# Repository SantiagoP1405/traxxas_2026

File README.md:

# traxxas_2026
Description will be added later.

Clone repository
```
cd
mkdir Workspaces/
cd Workspaces
mkdir traxxas_ws
cd traxxas_ws
git clone https://github.com/SantiagoP1405/traxxas_2026.git
mv traxxas_2026/ src/
colcon build
source install/setup.bash
```

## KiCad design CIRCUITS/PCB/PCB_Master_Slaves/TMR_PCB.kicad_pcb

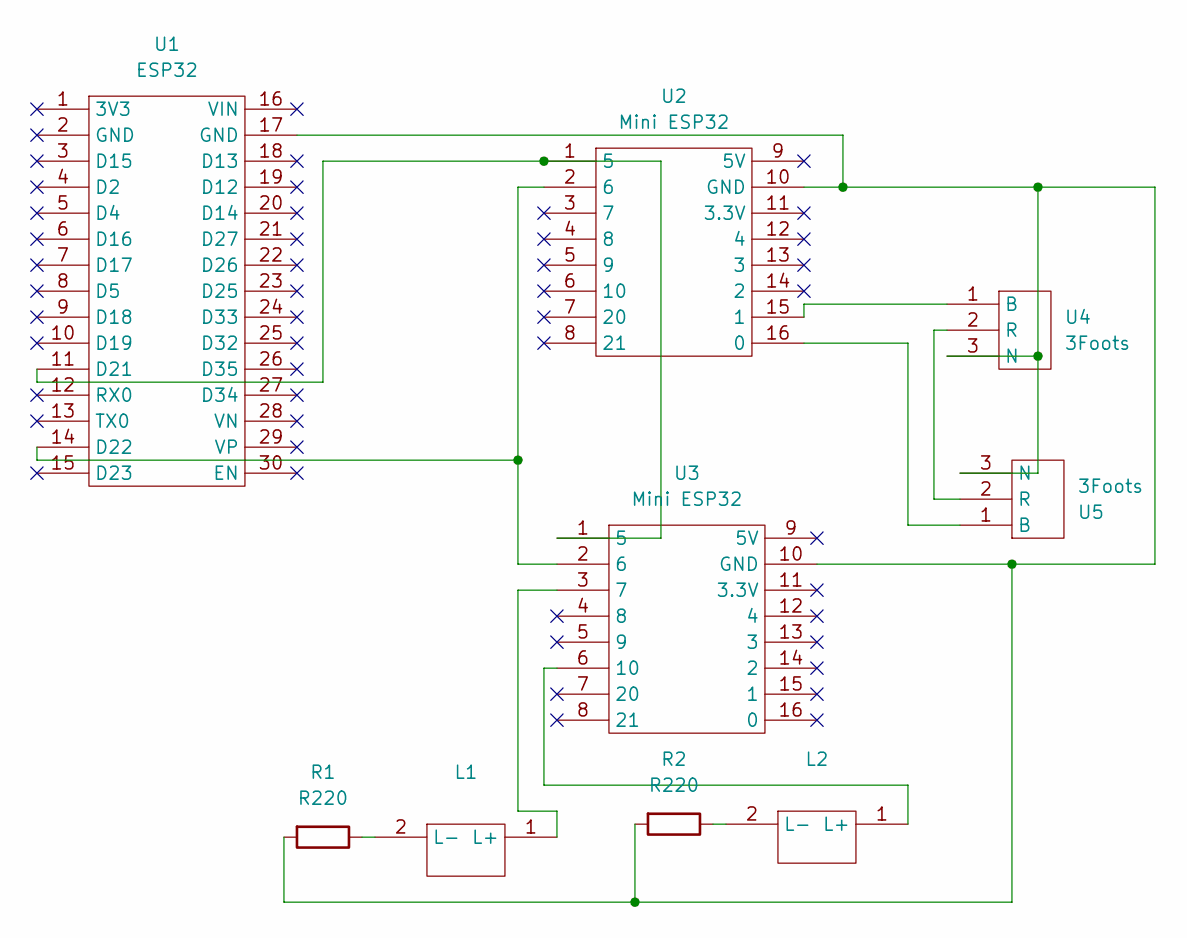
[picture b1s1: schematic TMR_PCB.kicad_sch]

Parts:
L1, L2: Leds
R1, R2: R220; R_Axial_DIN0207_L6.3mm_D2.5mm_P7.62mm_Horizontal
U1: ESP32
U2, U3: Mini ESP32
U4, U5: 3Foots

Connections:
unnamed: L1.1 (L+), U3.3 (7)
unnamed: L1.2 (L-), R1.1
unnamed: L2.1 (L+), U3.6 (10)
unnamed: L2.2 (L-), R2.1
unnamed: U1.11 (D21), U2.1 (5), U3.1 (5)
unnamed: U1.14 (D22), U2.2 (6), U3.2 (6)
unnamed: U2.16 (0), U5.1 (B)
unnamed: U2.15 (1), U4.1 (B)
unnamed: R1.2, R2.2, U1.17 (GND), U2.10 (GND), U3.10 (GND), U4.3 (N), U5.3 (N)
unnamed: U4.2 (R), U5.2 (R)

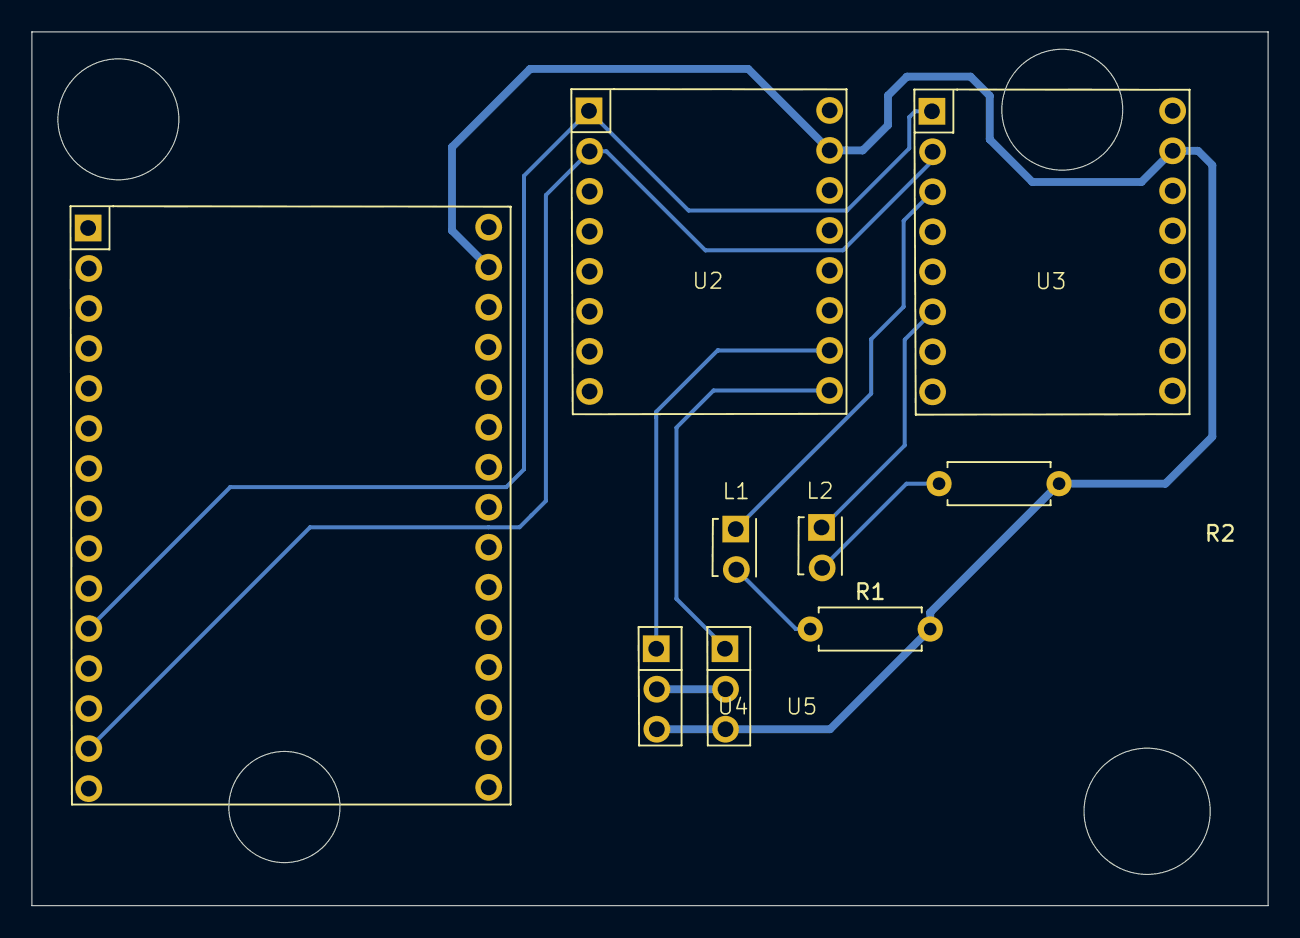
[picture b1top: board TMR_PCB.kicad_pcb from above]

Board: 2 copper layers, 78.5 x 55.5 mm, 9 parts (0 on the bottom side), 10 nets.

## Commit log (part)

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2025-12-15 Traxxas Motor Controler - Standalone Version
    ENG
    - micro-ROS code to control the steering servo and the Traxxas drive motor using 16-bit PWM signals at 100 Hz with a single ESP32.
    - Configuration of two PWM channels (ESP32 LEDC) for motor control:
    - PWM_R_CHANNEL (pin 23): Right motor (throttle)
    - PWM_L_CHANNEL (pin 18): Left motor (steering)
    - Frequency: 100 Hz, Resolution: 16 bits
2025-12-15 Traxxas Master Control I2C
2026-01-07 CIRCUITS
    ENG
    - Created circuits folder to store circuit diagrams and PCBs
    - Added diagram for the micro-ROS circuit
    ESP
    - Creada la carpeta para almacenar digramas de circuitos y PCBs.
    - Añadido diagramas para la red de micro-ROS
2026-01-11 gitignore
    ENG
    Add .gitignore
    ESP
    Añadido archivo .gitignore
2026-01-17 Traxxas urdf.xacro
    ENG
    - Added common properties XACRO file with material definitions (blue, green, grey, black, grey_dark) and inertia calculation macros for box, sphere, and cylinder shapes to standardize physical proper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
    - Implemented mobile base XACRO file defining chassis link with dimensions (length: 0.31m, width: 0.18m, height: 0.062m), mass calculated from density, and visual/collision geometries using box shape.
    - Included front and rear suspension links with specific dimensions, masses, and box geometries for realistic vehicle dynamics.
    - Defined wheel properties including radius (0.0535m), width (0.045m), density (900.0 kg/m³), and calculated mass usin
2026-01-17 RVIZ2 config
    ENG
    - Added configuration file for RViz2 visualization
    ESP
    - Añadido archivo de configuración para visualización en RViz2
2026-01-17 robot description - launch file
    ENG
    - Added ROS2 launch file display.launch.py for visualizing the Traxxas robot model in RViz, enabling interactive inspection of the robot's URDF structure and joint states.
    - Imported essential launch modules including LaunchDescription, Node, ParameterValue, Command, and Substitutions to handle dynamic parameter loading and command execution.
    - Utilized ament_index_python.packages.get_package_share_path to dynamically locate package share directories, ensuring portability across different ROS2 workspaces.
    - Defined paths for the XACRO URDF file (traxxas.urdf.xacro) and RViz configuration file (config.rviz) within the traxxas_robot_description package for o
2026-01-19 Implemented Gazebo plugins
    ENG
    - Added friction parameters (mu1, mu2) for all wheel links
    to enable realistic wheel-surface interactions in simulation
    - Integrated `gz-sim-ackermann-steering-system` plugin
    to simulate realistic Ackermann steering geometry with configurable steering limits and
    velocity constraints
2026-01-19 Traxxas Gazebo
    ENG
    - Created ROS2 package for the gazebo simulation of the Traxxas robot
    - Add robot simulation launch file (gz_sim.launch.py) that configures the complete simulation pipeline
    - Integrate ROS 2 with Gazebo Ignition through robot_state_publisher for kinematic chain updates
    Include spawn mechanism for robot model in Gazebo environment using robot description
    - Configure ros_gz_bridge with parameter-based bridge configuration for topic mapping
2026-01-20 Add Custom ZED2
    ENG
    - Implement ZED2 camera URDF Xacro model with right and left lens modules
    - Configure stereo camera sensors in Gazebo with Gaussian noise simulation
    - Add Gazebo plugins for image capture (640x480 resolution at 30 FPS)
    - Integrate ROS-Gazebo bridges for image and camera_info topics
    - Define optical frames with correct transformations for vision processing
2026-01-20 updated lens 'x' position
2026-01-20 Add Custom Lane follower Camera
    ENG
    - Create new camera_lane.xacro file with lane follower camera model
    - Include new camera in robot main assembly (traxxas.urdf.xacro)
    - Configure camera geometry, inertial properties and Gazebo sensors for lane follower
    - Add Gazebo-ROS bridge topics for lane follower camera image and camera_info streams
    - Add lane follower camera visualization to RViz configuration
2026-01-22 Add LiDAR sensor
    ENG
    - LiDAR sensor integration for the Traxxas robot.
    - LiDAR currently configured to have a 360° view for the /traxxas/scan topic.
    - LiDAR sensor to be used for autonomous parking
    ESP
    - Integración del sensor LiDAR para el robot Traxxas.
2026-01-23 Track World Integrated
    ENG
    - tools folder created.
    - Added Python code for .sdf Gazebo world generation using a .png image.
    - Base .png image and .sdf generator added to the tools folder.
    - worlds folder created.
    - new .sdf Gazebo world added to the worlds folder
2026-01-27 Create a 3d piece from the technical drawing versions for the Platform Deck, upside, down and joined
2026-01-29 Dual stereo camera lane detection with independent curve analysis
    Major refactoring of lane detection system to use both ZED camera eyes:
    Features:
    - Implemented dual-eye processing: left and right images analyzed independently
    - Separate lane detection pipeline for each camera perspective
    - Independent curvature calculations per eye for improved robustness
    - Enhanced black color filtering with morphological operations (CLOSE)
2026-01-31 Add all the files in AutoCAD and Inventor
2026-02-04 Created cmd_sim node
    ENG
    - Created ROS 2 Node
    - Implemented subscriber to topics /throttle_motor & /direction_servo to receive 14 bits PWM signals for both trhottle and direction
    - Maps received PWM values into -1 to 1 values to publish en /cmd_vel topic
    - Further work needed to correct steering, since the simulated robot in Gazebo shows maximum steering in both directions, despite the imput being intermediate values.
    ESP
2026-02-05 Reworked the lane detection pipeline using ZED stereo images and curvature-based steering control.
    Main changes:
    - Implemented black color filtering in HSV space as the primary lane segmentation method
    - Added aggressive morphological closing to reduce noise in black mask
    - Applied ROI masking after Canny edge detection to limit processing to relevant lane areas
    - Integrated perspective warp to generate a bird’s-eye view before lane fitting
    - Implemented sliding window lane detection on warped binary images
2026-02-06 Optimized lane detection pipeline with CUDA and ZED native functions
    Main changes:
    - Replaced original image processing pipeline with CUDA-accelerated functions for faster processing (down to 180ms).
    - Integrated ZED native functions for image retrieval to improve performance and reliability.
    - Replaced CPU-based filters with GPU-accelerated ones using OpenCV CUDA (CLAHE, Gaussian filter, Canny edge detection).
    - Updated the lane detection logic to support CUDA image processing, significantly improving processing speed.
    - Kept the existing sliding window and curvature calculation methods for lane detection.
2026-02-17 Enhanced lane detection robustness with noise filtering and stability improvements
    Main changes:
    - Added morphological operations (opening 11x11, closing 5x10) to reduce noise artifacts in binary threshold
    - Implemented masked Canny edge detection using white threshold as mask for cleaner edge detection
    - Added histogram smoothing with Gaussian blur (51px kernel) for more stable lane base detection
    - Added polynomial fit validation to reject invalid curvatures (|a| > 0.001, |b| > 5)
    - Implemented sliding window center movement constraint (max 40px jump) to prevent erratic tracking
2026-03-04 Updated robot simulation to operate with ZED common topics
2026-03-30 unify ultrasonic, IR sensors and battery on ESP32
    - Integrated 3 ultrasonic sensors and 1 IR sensor.
    - Fixed reading and calibration logic for the 3-cell LiPo battery.
    - Implemented multitasking with millis() to send data to ROS at 30Hz without OLED blocking.
2026-03-30 Add parking simulation package
    This package handles the autonomous parking simulation. It includes 3 core nodes:
    - lidar_processor: Reads and processes data from the LiDAR sensor.
    - fsm_parking: Finite State Machine that manages the parking logic and decisions.
    - parking_controller: Executes movement commands to drive the vehicle.
2026-03-31 Add Euler angle publishing to serial sensors node
    Added publishing of Euler angles to the Vector3Stamped topic.
2026-03-31 Stereo lane detection node with YOLO + Kalman filter: Implements a ROS2 node (LaneDetectorNode) that performs real-time lane detection using a YOLOv8 segmentation model (TensorRT) on both eyes of a Z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
    Key components:
    - ZED camera producer thread: reads frames from live camera or .svo2
    file and feeds a single-slot queue at ~10 fps
    - YOLO inference: runs batched segmentation on left+right frames using
    a .engine TRT model; masks are GPU-resized to original resolution
    - ROI + perspective warp: trapezoidal region of interest per eye is
2026-03-31 Added parking controller adapated to traxxas mechanics
2026-04-02 Modification: to setup files to make them compatible with newer versions of setuptools
2026-04-02 Updated parking system
2026-04-03 Changed serial port
2026-04-13 Update ESP32_battery_ultrasonic_infrared.ino
    Changed ECHO pin from D12 to D19 due to ESP32 boot issues
2026-04-14 Add validation for omega_motor in serial_sensors_node
2026-04-14 improvements in serial node and launch
2026-06-15 Moved Traxxas_V1 models and technical drawings to TRAXXAS_V1/MODEL & TRAXXAS_V1/ DRAW folders
2026-06-15 Moved CAD models
2026-06-15 Deleted joy_control.txt files
2026-06-15 Name changed
2026-06-15 On-board lane detector with 3-factor adaptive steering
    Monolithic node that runs on the car itself: it opens the ZED directly
    with pyzed and grabs frames in a producer thread, so capture, YOLO
    segmentation and control all live in one process.
    Per-eye pipeline: YOLO mask -> ROI -> bird's-eye warp -> sliding-window
    quadratic fit -> curvature. Steering is an adaptive fusion of three
    estimators (sliding-window curvature, linear slope of the warped lane,
2026-06-15 Pure-pursuit controller with real ZED undistortion
    External-PC node (subscribes to /zed/stereo/compressed) that steers with
    Pure Pursuit instead of the angle-fusion approach: it builds the BEV
    centerline from the left/right lane fits and aims at a look-ahead point
    (0.60 m) to compute the servo angle.
    Unlike the other variants, each eye is undistorted with the real
    intrinsics and distortion coefficients measured from our own ZED
2026-06-15 autonomous parallel-parking subsystem
    Add the four-node parallel-parking pipeline for the Traxxas:
    - fsm_parking3.py: high-level state machine (ParkingFSM3) that walks the
    maneuver ORIENTANDOSE -> BUSCAR_CAJA -> BUSCAR -> ESPERAR -> ALEJARSE
    -> ENTRAR_DIAGONAL -> ENDEREZAR -> ESTACIONANDO -> STOP, driven by
    perception flags and controller feedback; publishes /parking/state.
    - lidar_processor.py: bins the /scan ranges into front/right/left/rear
2026-06-15 Code modified to save a log
2026-06-15 launch file for the ZED-odometry parking stack
    Bring up the full parallel-parking system (the _28 visual-odometry
    variant) from a single launch:
    - includes the RPLIDAR A3 launch (serial port via the lidar_serial_port
    argument, default /dev/rplidar) and the traxxas_pose_estimation
    bringup (IMU, odometry and serial control);
    - starts the parking nodes: lane_detector_camara_28, lidar_processor,
2026-06-15 standalone HLS + Hough lane-angle prototype
    Add prueba.py, an offline sandbox (not a ROS node) for tuning the
    camera-only lane pipeline: reads a frame via cv2.VideoCapture, crops one
    lens of the stereo image, extracts white lane pixels in HLS, runs Canny
    + HoughLinesP over a ROI, fits the left/right lines and derives a
    steering angle from the lane-center offset, with EMA smoothing and a
    debug overlay. Used to prototype the approach before porting it into the
2026-06-16 Add firmware files for IMU and Encoder
    Two encoder+IMU firmware variants for AS5048A + BNO055, publishing CSV over Serial at 50 Hz for ROS2:
    - ESP32: publishes incremental distance (ds), encoder sampled at 2 kHz via micros()
    - ESP32-C3: publishes angular velocity (omega) using EMA filter over 100 ms window
2026-06-16 Add ROS2 obstacle avoidance nodes based on pose estimation with CSV routines - Add traxxas_obstacle_avoidance package - Update traxxas_pose_estimation node and launch - Pose-based logic not validated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
2026-06-16 Add traxxas_stop package ROS2 package that stops the vehicle on stop sign or crosswalk detection.
    Detection: stop_sign_node (HSV + contour) and crosswalk_node (stripe projection),
    each with a score-based confirmation filter. stop_event_merger_node combines both sources.
    Control: stop_routine_action_server runs a FSM (BrakeRamp→StopWait→ResumeRamp)
    with encoder feedback. pwm_controller handles throttle and steering PWM.
    traxxas_watchdog_node applies a safe brake if commands stop for >0.3 s.
2026-06-17 README.MD added
2026-06-17 PWM values mapped to real degrees depending on the motor
2026-06-19 Codes used to train de AI models added
2026-06-19 api keys deleted
2026-06-19 CAD REAME documentation README file added
2026-06-19 Add additional contributors to README
